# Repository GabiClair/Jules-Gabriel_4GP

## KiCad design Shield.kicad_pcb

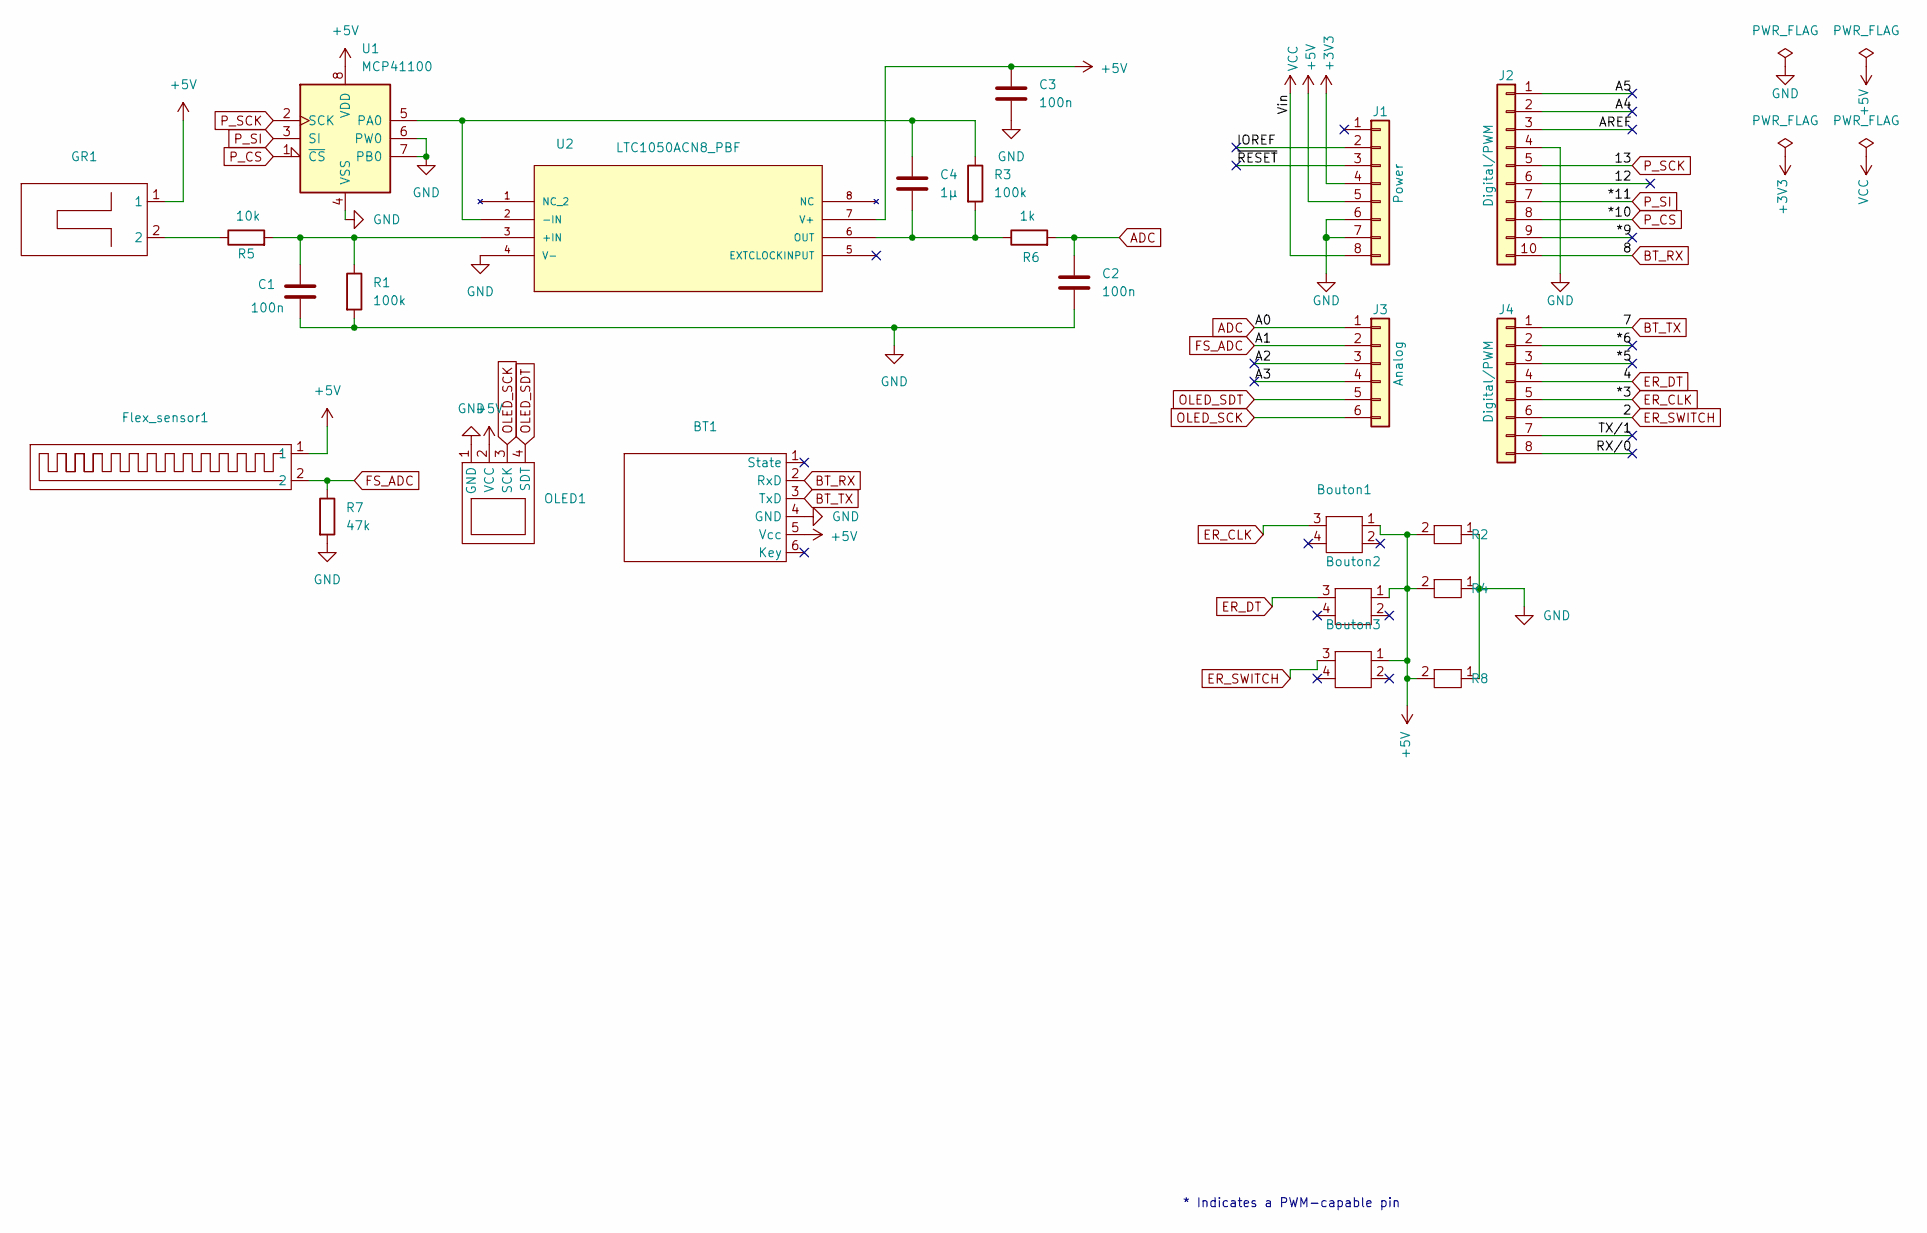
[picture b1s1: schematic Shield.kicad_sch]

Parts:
BT1: HT-05
Bouton1, Bouton2, Bouton3: Bouton
C1, C2, C3: 100n; CP_Radial_Tantal_D4.5mm_P5.00mm
C4: 1µ; C_Rect_L7.2mm_W4.5mm_P5.00mm_FKS2_FKP2_MKS2_MKP2
Flex_sensor1: Flex_Sensor
GR1: Capteur_GR
J1: Power; PinSocket_1x08_P2.54mm_Vertical
J2: Digital/PWM; PinSocket_1x10_P2.54mm_Vertical
J3: Analog; PinSocket_1x06_P2.54mm_Vertical
J4: Digital/PWM; PinSocket_1x08_P2.54mm_Vertical
OLED1: OLED
R1, R3: 100k; R_Axial_DIN0207_L6.3mm_D2.5mm_P10.16mm_Horizontal
R2, R4, R8: Res_debout
R5: 10k; R_Axial_DIN0207_L6.3mm_D2.5mm_P10.16mm_Horizontal
R6: 1k; R_Axial_DIN0207_L6.3mm_D2.5mm_P10.16mm_Horizontal
R7: 47k; R_Axial_DIN0207_L6.3mm_D2.5mm_P10.16mm_Horizontal
U1: MCP41100
U2: LTC1050ACN8_PBF; LTC1050; MANUFACTURER_PART_NUMBER ltc1050acn8

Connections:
+3V3: J1.4
+5V: BT1.5 (Vcc), Bouton1.1, Bouton2.1, Bouton3.1, C3.1, Flex_sensor1.1, GR1.1, J1.5, OLED1.2 (VCC), R2.2, R4.2, R8.2, U1.8 (VDD), U2.7 (V+)
/12: J2.6
/*5: J4.3
/*6: J4.2
/*9: J2.9
/A2: J3.3
/A3: J3.4
/A4: J2.2
/A5: J2.1
/AREF: J2.3
/IOREF: J1.2
/RX/0: J4.8
/TX/1: J4.7
/~RESET: J1.3
ADC: C2.1, J3.1, R6.2
BT_RX: BT1.2 (RxD), J2.10
BT_TX: BT1.3 (TxD), J4.1
ER_CLK: Bouton1.3, J4.5
ER_DT: Bouton2.3, J4.4
ER_SWITCH: Bouton3.3, J4.6
FS_ADC: Flex_sensor1.2, J3.2, R7.1
GND: BT1.4 (GND), C1.2, C2.2, C3.2, J1.6, J1.7, J2.4, OLED1.1 (GND), R1.2, R2.1, R4.1, R7.2, R8.1, U1.4 (VSS), U1.6 (PW0), U1.7 (PB0), U2.4 (V-)
unnamed: GR1.2, R5.1
unnamed: C4.1, R3.1, U1.5 (PA0), U2.2 (-IN)
unnamed: C1.1, R1.1, R5.2, U2.3 (+IN)
unnamed: C4.2, R3.2, R6.1, U2.6 (OUT)
OLED_SCK: J3.6, OLED1.3 (SCK)
OLED_SDT: J3.5, OLED1.4 (SDT)
P_CS: J2.8, U1.1 (~CS)
P_SCK: J2.5, U1.2 (SCK)
P_SI: J2.7, U1.3 (SI)
VCC: J1.8

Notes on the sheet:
* Indicates a PWM-capable pin

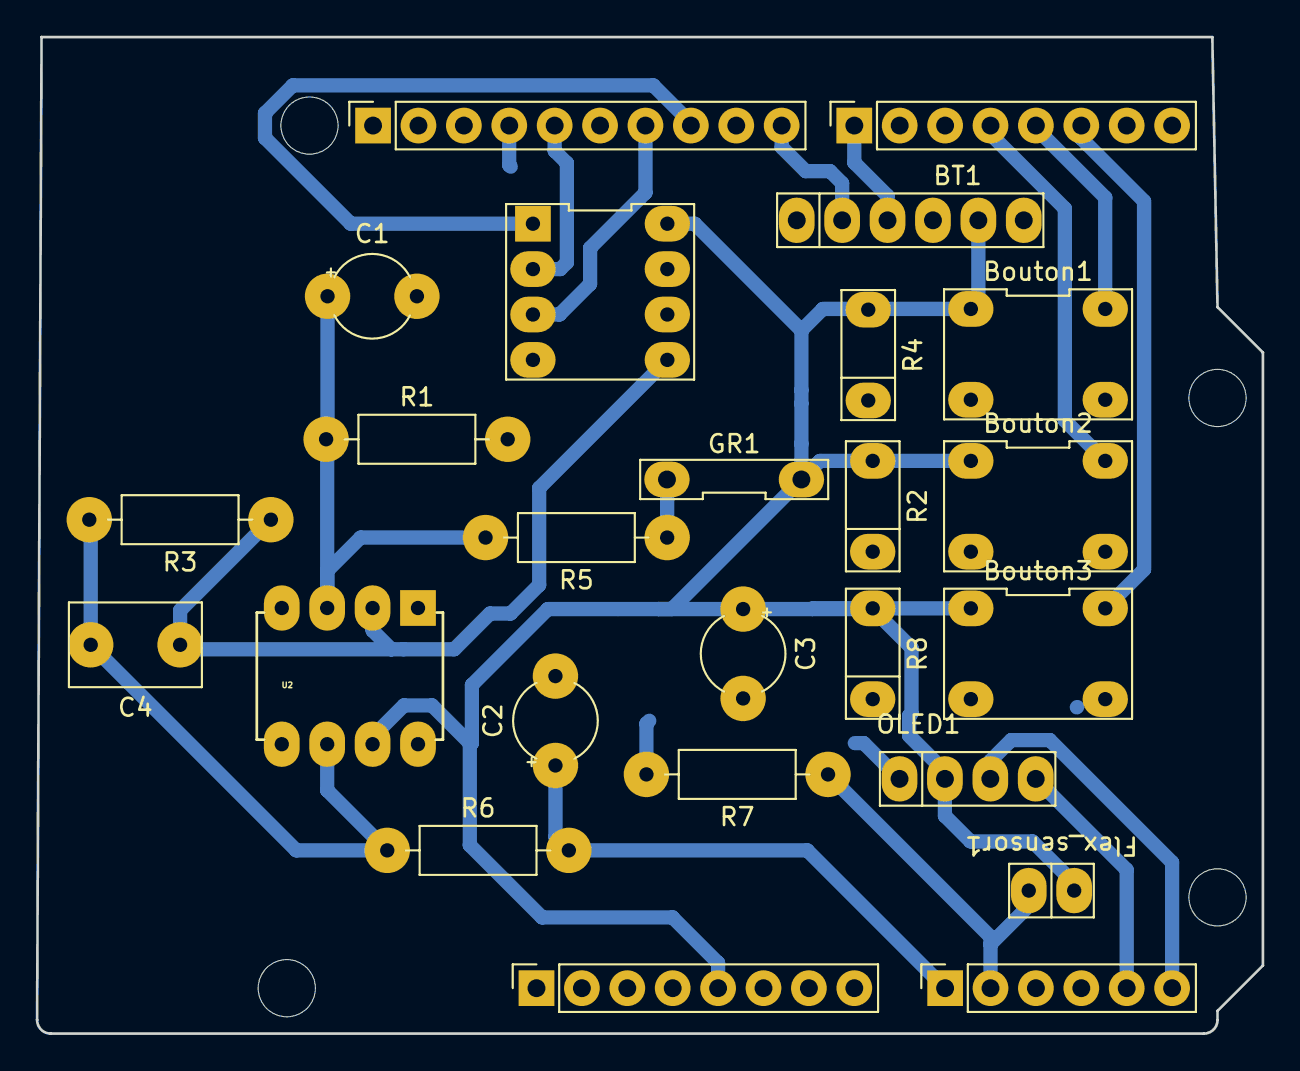
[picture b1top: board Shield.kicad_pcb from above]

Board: 2 copper layers, 68.6 x 55.8 mm, 29 parts (0 on the bottom side), 18 nets.

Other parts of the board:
MH1, MH2, MH3, MH4: MountingHole_3.2mm

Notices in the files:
parts and their libraries:
COPYRIGHT: Copyright C 2016 Accelerated Designs. All rights reserved
